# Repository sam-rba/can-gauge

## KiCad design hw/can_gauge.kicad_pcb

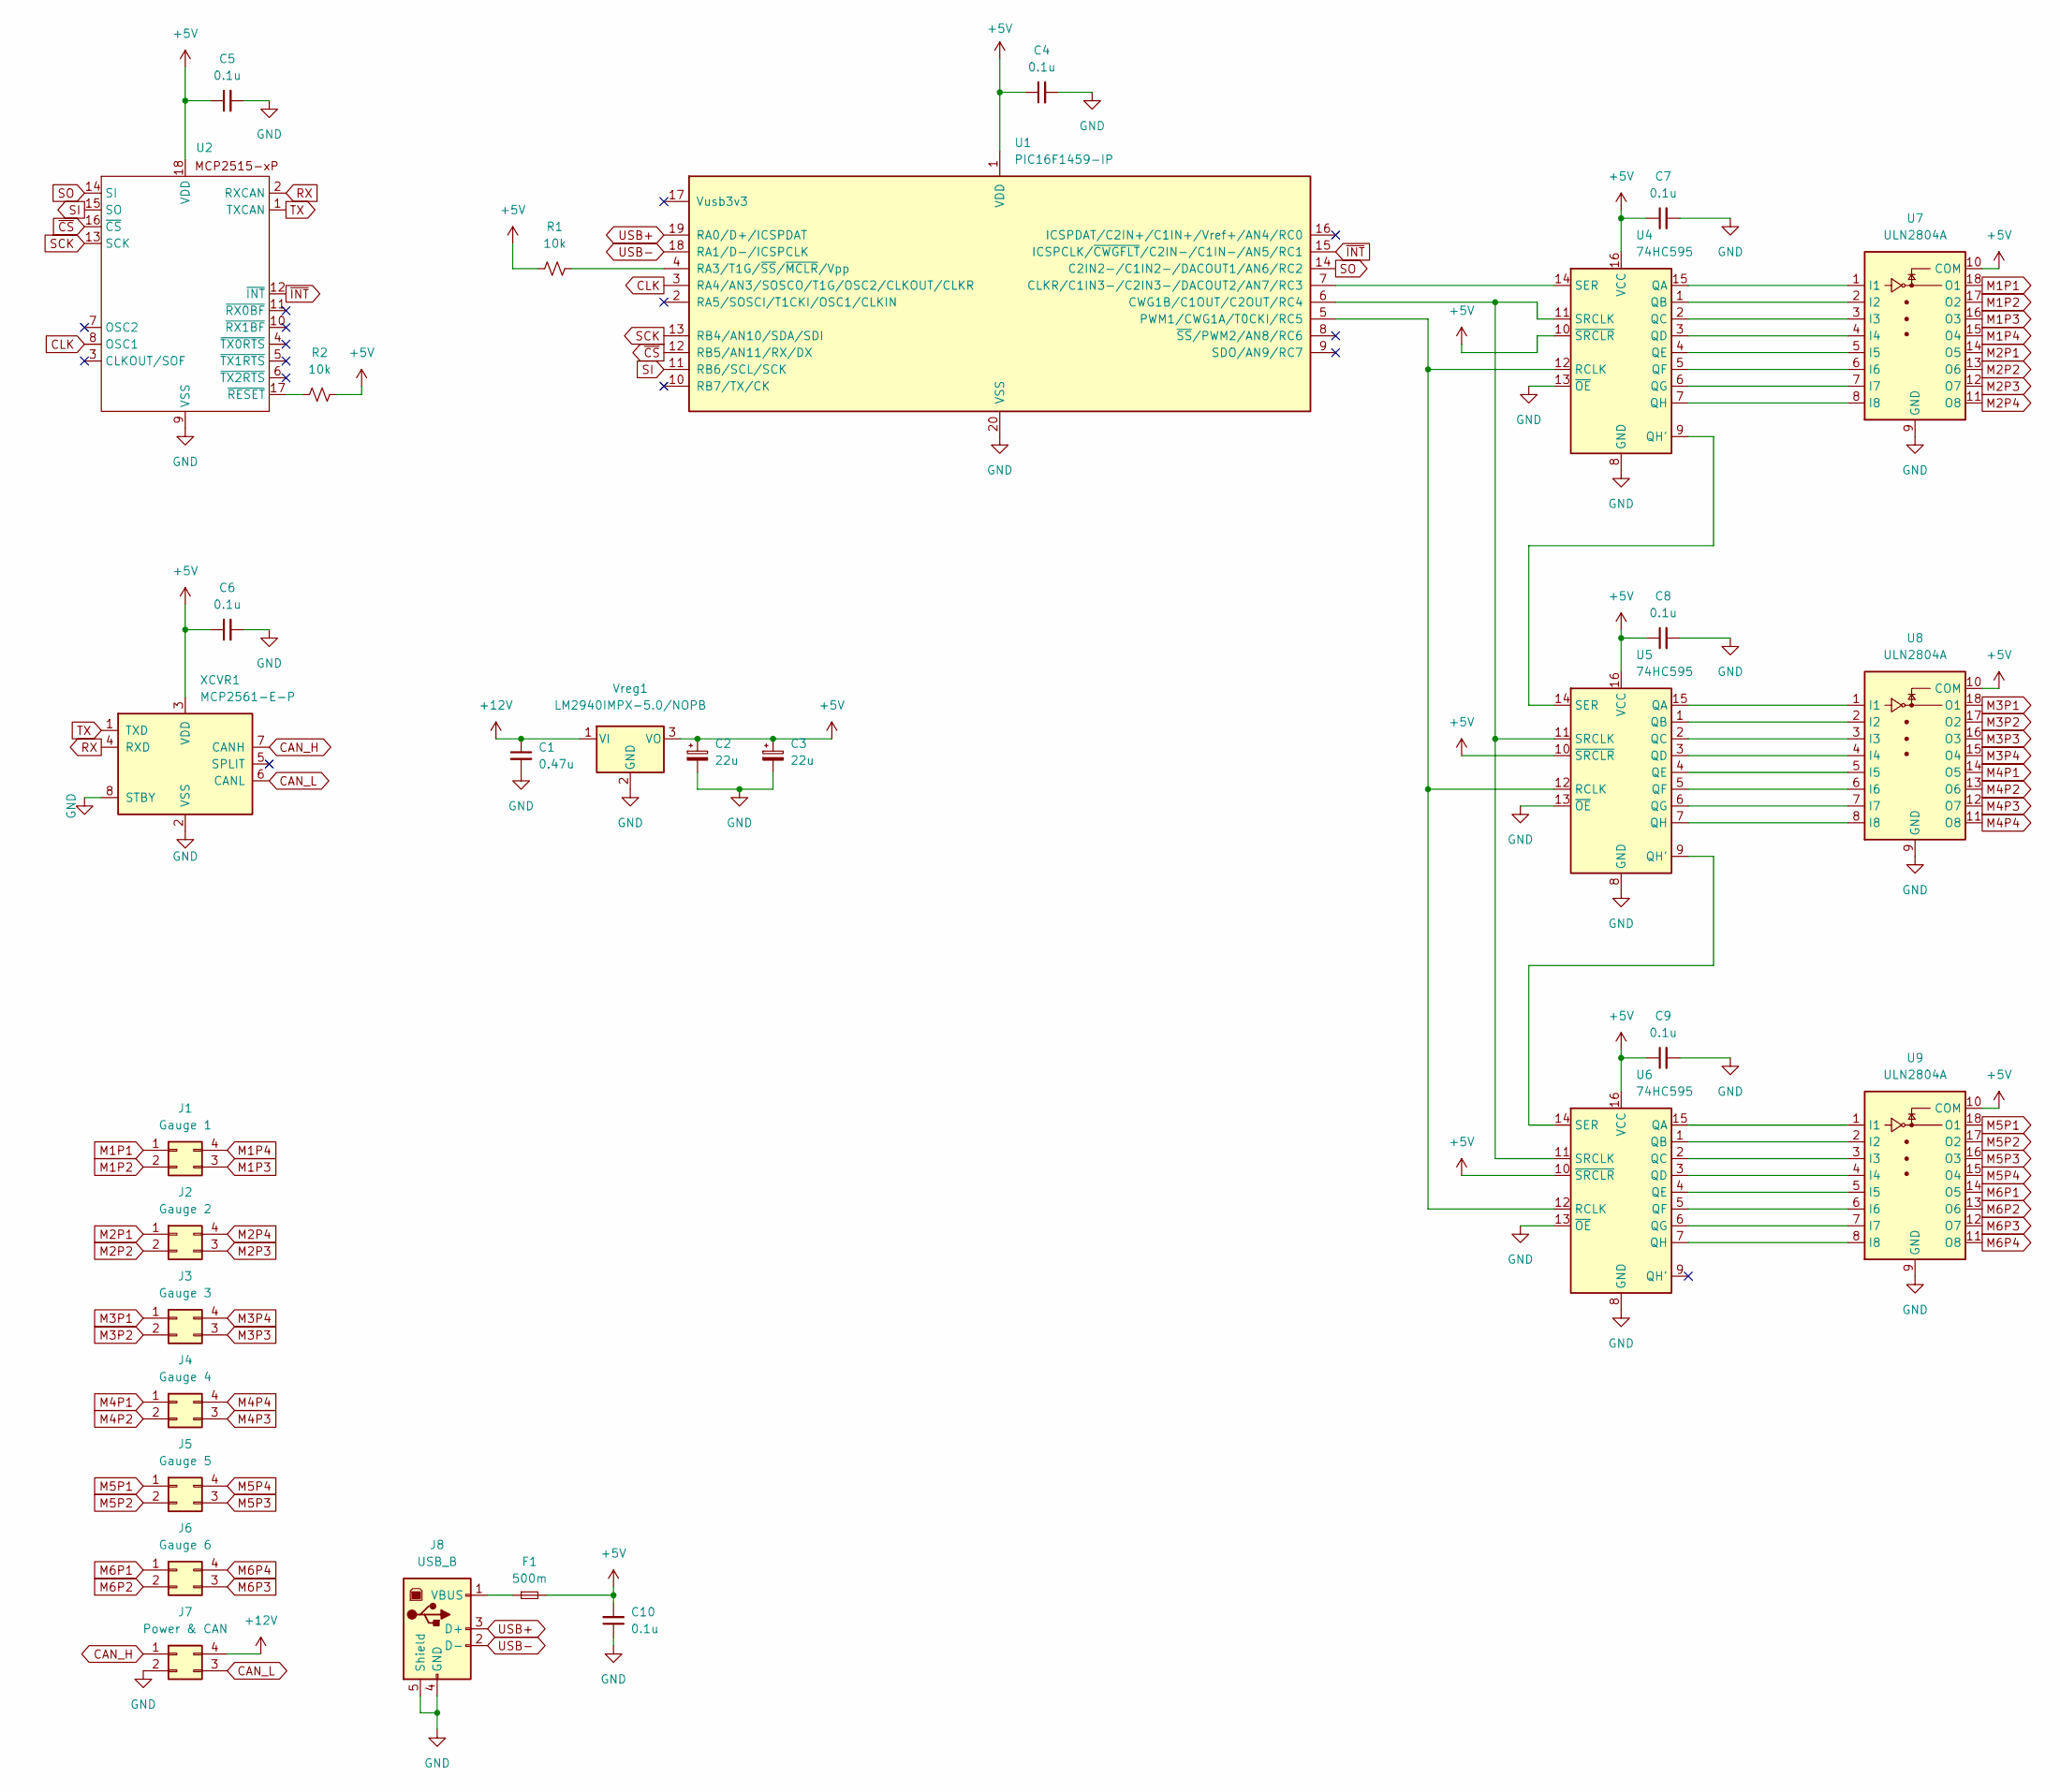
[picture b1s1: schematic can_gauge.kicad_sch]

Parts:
C1: 0.47u; C_0603_1608Metric
C2, C3: 22u; CP_EIA-6032-28_Kemet-C
C4, C5, C6, C7, C8, C9, C10: 0.1u; C_0603_1608Metric
F1: 500m; Fuse_0603_1608Metric
J1: Gauge 1; Molex_Mini-Fit_Jr_5569-04A2_2x02_P4.20mm_Horizontal
J2: Gauge 2; Molex_Mini-Fit_Jr_5569-04A2_2x02_P4.20mm_Horizontal
J3: Gauge 3; Molex_Mini-Fit_Jr_5569-04A2_2x02_P4.20mm_Horizontal
J4: Gauge 4; Molex_Mini-Fit_Jr_5569-04A2_2x02_P4.20mm_Horizontal
J5: Gauge 5; Molex_Mini-Fit_Jr_5569-04A2_2x02_P4.20mm_Horizontal
J6: Gauge 6; Molex_Mini-Fit_Jr_5569-04A2_2x02_P4.20mm_Horizontal
J7: Power & CAN; Molex_Mini-Fit_Jr_5569-04A2_2x02_P4.20mm_Horizontal
J8: USB_B; UJ2-BH-BL1-TH
R1, R2: 10k; R_0805_2012Metric
U1: PIC16F1459-IP; DIP-20_W7.62mm
U2: MCP2515-IP; DIP-18_W7.62mm
U4, U5, U6: 74HC595; DIP-16_W7.62mm
U7, U8, U9: ULN2804A; DIP-18_W7.62mm
Vreg1: LM2940IMPX-5.0/NOPB; SOT-223
XCVR1: MCP2561-E-P; DIP-8_W7.62mm

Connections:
+5V: C2.1, C3.1, C4.1, C5.1, C6.1, C7.1, C8.1, C9.1, C10.2, F1.2, R1.1, R2.2, U1.1 (VDD), U2.18 (VDD), U4.10 (~SRCLR), U4.16 (VCC), U5.10 (~SRCLR), U5.16 (VCC), U6.10 (~SRCLR), U6.16 (VCC), U7.10 (COM), U8.10 (COM), U9.10 (COM), Vreg1.3 (VO), XCVR1.3 (VDD)
+12V: C1.1, J7.4, Vreg1.1 (VI)
CAN_H: J7.1, XCVR1.7 (CANH)
CAN_L: J7.3, XCVR1.6 (CANL)
CLK: U1.3 (RA4/AN3/SOSCO/T1G/OSC2/CLKOUT/CLKR), U2.8 (OSC1)
GND: C1.2, C2.2, C3.2, C4.2, C5.2, C6.2, C7.2, C8.2, C9.2, C10.1, J7.2, J8.4 (GND), J8.5 (Shield), U1.20 (VSS), U2.9 (VSS), U4.8 (GND), U4.13 (~OE), U5.8 (GND), U5.13 (~OE), U6.8 (GND), U6.13 (~OE), U7.9 (GND), U8.9 (GND), U9.9 (GND), Vreg1.2 (GND), XCVR1.2 (VSS), XCVR1.8 (STBY)
M1P1: J1.1, U7.18 (O1)
M1P2: J1.2, U7.17 (O2)
M1P3: J1.3, U7.16 (O3)
M1P4: J1.4, U7.15 (O4)
M2P1: J2.1, U7.14 (O5)
M2P2: J2.2, U7.13 (O6)
M2P3: J2.3, U7.12 (O7)
M2P4: J2.4, U7.11 (O8)
M3P1: J3.1, U8.18 (O1)
M3P2: J3.2, U8.17 (O2)
M3P3: J3.3, U8.16 (O3)
M3P4: J3.4, U8.15 (O4)
M4P1: J4.1, U8.14 (O5)
M4P2: J4.2, U8.13 (O6)
M4P3: J4.3, U8.12 (O7)
M4P4: J4.4, U8.11 (O8)
M5P1: J5.1, U9.18 (O1)
M5P2: J5.2, U9.17 (O2)
M5P3: J5.3, U9.16 (O3)
M5P4: J5.4, U9.15 (O4)
M6P1: J6.1, U9.14 (O5)
M6P2: J6.2, U9.13 (O6)
M6P3: J6.3, U9.12 (O7)
M6P4: J6.4, U9.11 (O8)
unnamed: F1.1, J8.1 (VBUS)
unnamed: U1.7 (CLKR/C1IN3-/C2IN3-/DACOUT2/AN7/RC3), U4.14 (SER)
unnamed: U1.6 (CWG1B/C1OUT/C2OUT/RC4), U4.11 (SRCLK), U5.11 (SRCLK), U6.11 (SRCLK)
unnamed: U1.5 (PWM1/CWG1A/T0CKI/RC5), U4.12 (RCLK), U5.12 (RCLK), U6.12 (RCLK)
unnamed: R1.2, U1.4 (RA3/T1G/~SS/~MCLR/Vpp)
unnamed: R2.1, U2.17 (~RESET)
unnamed: U4.15 (QA), U7.1 (I1)
unnamed: U4.1 (QB), U7.2 (I2)
unnamed: U4.2 (QC), U7.3 (I3)
unnamed: U4.3 (QD), U7.4 (I4)
unnamed: U4.4 (QE), U7.5 (I5)
unnamed: U4.5 (QF), U7.6 (I6)
unnamed: U4.6 (QG), U7.7 (I7)
unnamed: U4.9 (QH'), U5.14 (SER)
unnamed: U4.7 (QH), U7.8 (I8)
unnamed: U5.15 (QA), U8.1 (I1)
unnamed: U5.1 (QB), U8.2 (I2)
unnamed: U5.2 (QC), U8.3 (I3)
unnamed: U5.3 (QD), U8.4 (I4)
unnamed: U5.4 (QE), U8.5 (I5)
unnamed: U5.5 (QF), U8.6 (I6)
unnamed: U5.6 (QG), U8.7 (I7)
unnamed: U5.9 (QH'), U6.14 (SER)
unnamed: U5.7 (QH), U8.8 (I8)
unnamed: U6.15 (QA), U9.1 (I1)
unnamed: U6.1 (QB), U9.2 (I2)
unnamed: U6.2 (QC), U9.3 (I3)
unnamed: U6.3 (QD), U9.4 (I4)
unnamed: U6.4 (QE), U9.5 (I5)
unnamed: U6.5 (QF), U9.6 (I6)
unnamed: U6.6 (QG), U9.7 (I7)
unnamed: U6.7 (QH), U9.8 (I8)
RX: U2.2 (RXCAN), XCVR1.4 (RXD)
SCK: U1.13 (RB4/AN10/SDA/SDI), U2.13 (SCK)
SI: U1.11 (RB6/SCL/SCK), U2.15 (SO)
SO: U1.14 (C2IN2-/C1IN2-/DACOUT1/AN6/RC2), U2.14 (SI)
TX: U2.1 (TXCAN), XCVR1.1 (TXD)
USB+: J8.3 (D+), U1.19 (RA0/D+/ICSPDAT)
USB-: J8.2 (D-), U1.18 (RA1/D-/ICSPCLK)
~CS: U1.12 (RB5/AN11/RX/DX), U2.16 (~CS)
~INT: U1.15 (ICSPCLK/~CWGFLT/C2IN-/C1IN-/AN5/RC1), U2.12 (~INT)

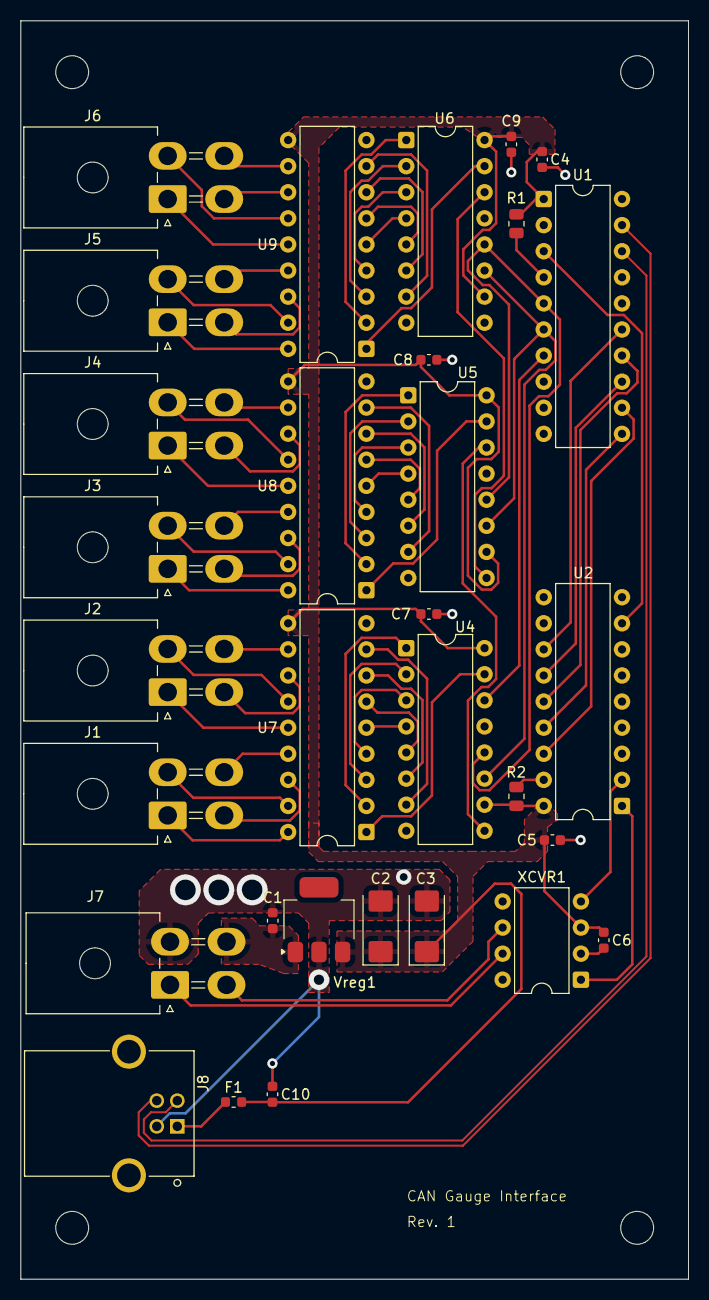
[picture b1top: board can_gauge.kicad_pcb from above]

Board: 2 copper layers, 65.0 x 122.5 mm, 31 parts (0 on the bottom side), 71 nets.

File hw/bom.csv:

"Reference","Qty","Value","DNP","Exclude from BOM","Exclude from Board","Footprint","Datasheet"
"C1","1","0.47u","","","","Capacitor_SMD:C_0603_1608Metric","https://mm.digikey.com/Volume0/opasdata/d220001/medias/docus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"
"C2,C3","2","22u","","","","Capacitor_Tantalum_SMD:CP_EIA-6032-28_Kemet-C","https://datasheets.kyocera-avx.com/TAJ_AUTO.pdf"
"C4,C5,C6,C7,C8,C9,C10","7","0.1u","","","","Capacitor_THT:C_Rect_L4.0mm_W2.5mm_P2.50mm","https://product.tdk.com/en/system/files/dam/doc/product/capa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"
"F1","1","500m","","","","Fuse:Fuse_0402_1005Metric","http://www.kamaya.co.jp/upload/products_pdf/kamaya_products(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"
"J1","1","Gauge 1","","","","Connector_Molex:Molex_Mini-Fit_Jr_5569-04A2_2x02_P4.20mm_Horizontal","https://www.molex.com/en-us/products/part-detail/39301040?di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"
"J2","1","Gauge 2","","","","Connector_Molex:Molex_Mini-Fit_Jr_5569-04A2_2x02_P4.20mm_Horizontal","https://www.molex.com/en-us/products/part-detail/39301040?di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"
"J3","1","Gauge 3","","","","Connector_Molex:Molex_Mini-Fit_Jr_5569-04A2_2x02_P4.20mm_Horizontal","https://www.molex.com/en-us/products/part-detail/39301040?di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"
"J4","1","Gauge 4","","","","Connector_Molex:Molex_Mini-Fit_Jr_5569-04A2_2x02_P4.20mm_Horizontal","https://www.molex.com/en-us/products/part-detail/39301040?di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"
"J5","1","Gauge 5","","","","Connector_Molex:Molex_Mini-Fit_Jr_5569-04A2_2x02_P4.20mm_Horizontal","https://www.molex.com/en-us/products/part-detail/39301040?di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"
"J6","1","Gauge 6","","","","Connector_Molex:Molex_Mini-Fit_Jr_5569-04A2_2x02_P4.20mm_Horizontal","https://www.molex.com/en-us/products/part-detail/39301040?di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"
"J7","1","Power & CAN","","","","Connector_Molex:Molex_Mini-Fit_Jr_5569-04A2_2x02_P4.20mm_Horizontal","https://www.molex.com/en-us/products/part-detail/39301040?di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"
"J8","1","USB_B","","","","footprints:UJ2-BH-BL1-TH","https://www.cuidevices.com/product/resource/uj2-bh-th.pdf"
"R1,R2","2","10k","","","","Resistor_SMD:R_0402_1005Metric","https://industrial.panasonic.com/cdbs/www-data/pdf/RDA0000/A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"
"U1","1","PIC16F1459-IP","","","","Package_DIP:DIP-20_W7.62mm","http://ww1.microchip.com/downloads/en/DeviceDoc/41639A.pdf"
"U2","1","~","","","","Package_DIP:DIP-18_W7.62mm","https://ww1.microchip.com/downloads/aemDocuments/documents/A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"
"U4,U5,U6","3","74HC595","","","","Package_DIP:DIP-16_W7.62mm","https://www.ti.com/general/docs/suppproductinfo.tsp?distId=1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"
"U7,U8,U9","3","ULN2804A","","","","Package_DIP:DIP-18_W7.62mm","https://www.st.com/content/ccc/resource/technical/document/d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"
"Vreg1","1","LM2940IMPX-5.0/NOPB","","","","Package_TO_SOT_SMD:SOT-223","https://www.ti.com/general/docs/suppproductinfo.tsp?distId=1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"
"XCVR1","1","MCP2561-E-P","","","","Package_DIP:DIP-8_W7.62mm","http://ww1.microchip.com/downloads/en/DeviceDoc/25167A.pdf"

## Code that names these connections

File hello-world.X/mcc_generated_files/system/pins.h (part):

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// get/set IO_RB4 aliases
#define SO_TRIS                 TRISBbits.TRISB4
#define SO_LAT                  LATBbits.LATB4
#define SO_PORT                 PORTBbits.RB4
#define SO_WPU                  WPUBbits.WPUB4
#define SO_OD                   ODCONBbits.ODB4
#define SO_ANS                  ANSELBbits.ANSB4
#define SO_SetHigh()            do { LATBbits.LATB4 = 1; } while(0)
#define SO_SetLow()             do { LATBbits.LATB4 = 0; } while(0)
#define SO_Toggle()             do { LATBbits.LATB4 = ~LATBbits.LATB4; } while(0)
#define SO_GetValue()           PORTBbits.RB4
#define SO_SetDigitalInput()    do { TRISBbits.TRISB4 = 1; } while(0)
#define SO_SetDigitalOutput()   do { TRISBbits.TRISB4 = 0; } while(0)
#define SO_SetPullup()          do { WPUBbits.WPUB4 = 1; } while(0)
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// get/set IO_RB5 aliases
#define SCLK_TRIS                 TRISBbits.TRISB5
#define SCLK_LAT                  LATBbits.LATB5
#define SCLK_PORT                 PORTBbits.RB5
#define SCLK_WPU                  WPUBbits.WPUB5
#define SCLK_OD                   ODCONBbits.ODB5
#define SCLK_ANS                  ANSELBbits.ANSB5
#define SCLK_SetHigh()            do { LATBbits.LATB5 = 1; } while(0)
#define SCLK_SetLow()             do { LATBbits.LATB5 = 0; } while(0)
#define SCLK_Toggle()             do { LATBbits.LATB5 = ~LATBbits.LATB5; } while(0)
#define SCLK_GetValue()           PORTBbits.RB5
#define SCLK_SetDigitalInput()    do { TRISBbits.TRISB5 = 1; } while(0)
#define SCLK_SetDigitalOutput()   do { TRISBbits.TRISB5 = 0; } while(0)
#define SCLK_SetPullup()          do { WPUBbits.WPUB5 = 1; } while(0)
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// get/set IO_RB6 aliases
#define CS_TRIS                 TRISBbits.TRISB6
#define CS_LAT                  LATBbits.LATB6
#define CS_PORT                 PORTBbits.RB6
#define CS_WPU                  WPUBbits.WPUB6
#define CS_OD                   ODCONBbits.ODB6
#define CS_ANS                  ANSELBbits.ANSB6
#define CS_SetHigh()            do { LATBbits.LATB6 = 1; } while(0)
#define CS_SetLow()             do { LATBbits.LATB6 = 0; } while(0)
#define CS_Toggle()             do { LATBbits.LATB6 = ~LATBbits.LATB6; } while(0)
#define CS_GetValue()           PORTBbits.RB6
#define CS_SetDigitalInput()    do { TRISBbits.TRISB6 = 1; } while(0)
#define CS_SetDigitalOutput()   do { TRISBbits.TRISB6 = 0; } while(0)
#define CS_SetPullup()          do { WPUBbits.WPUB6 = 1; } while(0)
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// get/set IO_RC1 aliases
#define MOTOR_01_TRIS                 TRISCbits.TRISC1
#define MOTOR_01_LAT                  LATCbits.LATC1
#define MOTOR_01_PORT                 PORTCbits.RC1
#define MOTOR_01_WPU                  WPUCbits.WPUC1
#define MOTOR_01_OD                   ODCONCbits.ODC1
#define MOTOR_01_ANS                  ANSELCbits.ANSC1
#define MOTOR_01_SetHigh()            do { LATCbits.LATC1 = 1; } while(0)
#define MOTOR_01_SetLow()             do { LATCbits.LATC1 = 0; } while(0)
#define MOTOR_01_Toggle()             do { LATCbits.LATC1 = ~LATCbits.LATC1; } while(0)
#define MOTOR_01_GetValue()           PORTCbits.RC1
#define MOTOR_01_SetDigitalInput()    do { TRISCbits.TRISC1 = 1; } while(0)
#define MOTOR_01_SetDigitalOutput()   do { TRISCbits.TRISC1 = 0; } while(0)
#define MOTOR_01_SetPullup()          do { WPUCbits.WPUC1 = 1; } while(0)
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// get/set IO_RC2 aliases
#define MOTOR_02_TRIS                 TRISCbits.TRISC2
#define MOTOR_02_LAT                  LATCbits.LATC2
#define MOTOR_02_PORT                 PORTCbits.RC2
#define MOTOR_02_WPU                  WPUCbits.WPUC2
#define MOTOR_02_OD                   ODCONCbits.ODC2
#define MOTOR_02_ANS                  ANSELCbits.ANSC2
#define MOTOR_02_SetHigh()            do { LATCbits.LATC2 = 1; } while(0)
#define MOTOR_02_SetLow()             do { LATCbits.LATC2 = 0; } while(0)
#define MOTOR_02_Toggle()             do { LATCbits.LATC2 = ~LATCbits.LATC2; } while(0)
#define MOTOR_02_GetValue()           PORTCbits.RC2
#define MOTOR_02_SetDigitalInput()    do { TRISCbits.TRISC2 = 1; } while(0)
#define MOTOR_02_SetDigitalOutput()   do { TRISCbits.TRISC2 = 0; } while(0)
#define MOTOR_02_SetPullup()          do { WPUCbits.WPUC2 = 1; } while(0)
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// get/set IO_RC3 aliases
#define MOTOR_03_TRIS                 TRISCbits.TRISC3
#define MOTOR_03_LAT                  LATCbits.LATC3
#define MOTOR_03_PORT                 PORTCbits.RC3
#define MOTOR_03_WPU                  WPUCbits.WPUC3
#define MOTOR_03_OD                   ODCONCbits.ODC3
#define MOTOR_03_ANS                  ANSELCbits.ANSC3
#define MOTOR_03_SetHigh()            do { LATCbits.LATC3 = 1; } while(0)
#define MOTOR_03_SetLow()             do { LATCbits.LATC3 = 0; } while(0)
#define MOTOR_03_Toggle()             do { LATCbits.LATC3 = ~LATCbits.LATC3; } while(0)
#define MOTOR_03_GetValue()           PORTCbits.RC3
#define MOTOR_03_SetDigitalInput()    do { TRISCbits.TRISC3 = 1; } while(0)
#define MOTOR_03_SetDigitalOutput()   do { TRISCbits.TRISC3 = 0; } while(0)
#define MOTOR_03_SetPullup()          do { WPUCbits.WPUC3 = 1; } while(0)
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// get/set IO_RC4 aliases
#define MOTOR_10_TRIS                 TRISCbits.TRISC4
#define MOTOR_10_LAT                  LATCbits.LATC4
#define MOTOR_10_PORT                 PORTCbits.RC4
#define MOTOR_10_WPU                  WPUCbits.WPUC4
#define MOTOR_10_OD                   ODCONCbits.ODC4
#define MOTOR_10_ANS                  ANSELCbits.
#define MOTOR_10_SetHigh()            do { LATCbits.LATC4 = 1; } while(0)
#define MOTOR_10_SetLow()             do { LATCbits.LATC4 = 0; } while(0)
#define MOTOR_10_Toggle()             do { LATCbits.LATC4 = ~LATCbits.LATC4; } while(0)
#define MOTOR_10_GetValue()           PORTCbits.RC4
#define MOTOR_10_SetDigitalInput()    do { TRISCbits.TRISC4 = 1; } while(0)
#define MOTOR_10_SetDigitalOutput()   do { TRISCbits.TRISC4 = 0; } while(0)
#define MOTOR_10_SetPullup()          do { WPUCbits.WPUC4 = 1; } while(0)
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// get/set IO_RC5 aliases
#define MOTOR_11_TRIS                 TRISCbits.TRISC5
#define MOTOR_11_LAT                  LATCbits.LATC5
#define MOTOR_11_PORT                 PORTCbits.RC5
#define MOTOR_11_WPU                  WPUCbits.WPUC5
#define MOTOR_11_OD                   ODCONCbits.ODC5
#define MOTOR_11_ANS                  ANSELCbits.
#define MOTOR_11_SetHigh()            do { LATCbits.LATC5 = 1; } while(0)
#define MOTOR_11_SetLow()             do { LATCbits.LATC5 = 0; } while(0)
#define MOTOR_11_Toggle()             do { LATCbits.LATC5 = ~LATCbits.LATC5; } while(0)
#define MOTOR_11_GetValue()           PORTCbits.RC5
#define MOTOR_11_SetDigitalInput()    do { TRISCbits.TRISC5 = 1; } while(0)
#define MOTOR_11_SetDigitalOutput()   do { TRISCbits.TRISC5 = 0; } while(0)
#define MOTOR_11_SetPullup()          do { WPUCbits.WPUC5 = 1; } while(0)
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
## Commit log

2025-06-03 datasheets
2025-06-03 bom and kicad project
2025-06-03 old mplab project
2025-06-03 new mplab project
2025-06-03 add libreoffice lock file to gitignore
2025-06-03 sn74hc595 datasheet
2025-06-03 generate mplab config
2025-06-03 copy old files to new mplab project
2025-06-03 mplab file
2025-06-25 makefile
2025-06-25 clang-format
2025-06-26 format generated files
2025-06-26 mcp2561 datasheet
2025-06-26 mcp2515 falling edge interrupt
2025-06-26 hw: power and ground
2025-06-27 hw: mcp2515 serial lines
2025-06-28 hw: mcp2515 reset
2025-06-28 hw: pic/mcp clock line
2025-06-28 hw: serial line labels
2025-06-28 uln2003a datasheet
2025-06-28 hw: connector
2025-06-28 hw: motor drivers
2025-06-28 regen mcc config
    Changed shift register pin assignments
    Enabled CLKOUT
    Disabled MCLR
2025-06-28 hw: shift registers
2025-06-28 pic16f1454 datasheet
2025-06-28 sw: switch to pic16f1459
2025-06-28 hw: switch to pic16f1459
2025-06-29 hw: ldo caps
2025-06-30 hw: rename ICs
2025-06-30 hw: not terminating node
2025-06-30 hw: ic footprints
2025-07-01 hw: rename passives
2025-07-01 hw: passive footprints
2025-07-01 hw: pcb layout
2025-07-01 hw: change connector layout
2025-07-01 hw: 8-way transistor arrays, 6 gauges
2025-07-01 hw: shift register placement
2025-07-01 hw: through-hole shift registers
2025-07-01 hw: partial uc layout
2025-07-01 hw: vreg placement
2025-07-01 hw: data traces
2025-07-01 hw: move shift register and position xcvr
2025-07-01 hw: rx,tx traces
2025-07-01 hw: mcp2515 traces
2025-07-01 hw: extend power plane
2025-07-02 hw: power plane
2025-07-02 hw: xcvr gnd plane
2025-07-02 hw: transistor array gnd plane
2025-07-02 hw: uc gnd plane
2025-07-02 hw: gnd plane
2025-07-04 hw: remove redundant vias on though-holes
2025-07-04 hw: power supply vias
2025-07-04 hw: remove redundant via
2025-07-04 hw: fix errors
2025-07-04 hw: USB port
2025-07-05 hw: board outline and 3d models
2025-07-05 hw: schematic page setup; fix usb wiring
2025-07-05 hw: shrink board
2025-07-05 hw: fix clipped silkscreen
2025-07-05 hw: generate bom and cpl
2025-07-05 hw: smd caps
2025-07-05 remove bom
2025-07-05 hw: larger package caps
2025-07-05 larger package resistors and fuse
2025-07-05 uln2804 datasheet
2025-07-05 rev 1 quote
2025-07-05 digital pot
2025-07-08 hw: rev 2 pic and mcp2515 schematic
2025-07-13 eeprom
2025-07-13 dacs
2025-07-13 warning light outputs
2025-07-13 fix usb wiring

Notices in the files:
hello-world.X/mcc_generated_files/system/pins.h:
© [2025] Microchip Technology Inc. and its subsidiaries.
